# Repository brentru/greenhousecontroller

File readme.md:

# Greenhouse Control System
##  Project for ECE388

----
## Hardware

Greenboard: Control board for small-scale greenhouse control running off an ATMEGA328P.

----
## Software
Production: ATMEL Studio 7
Proto: Arduino 

----
## thanks
* David A.
* Jarred T.
* Brent R.

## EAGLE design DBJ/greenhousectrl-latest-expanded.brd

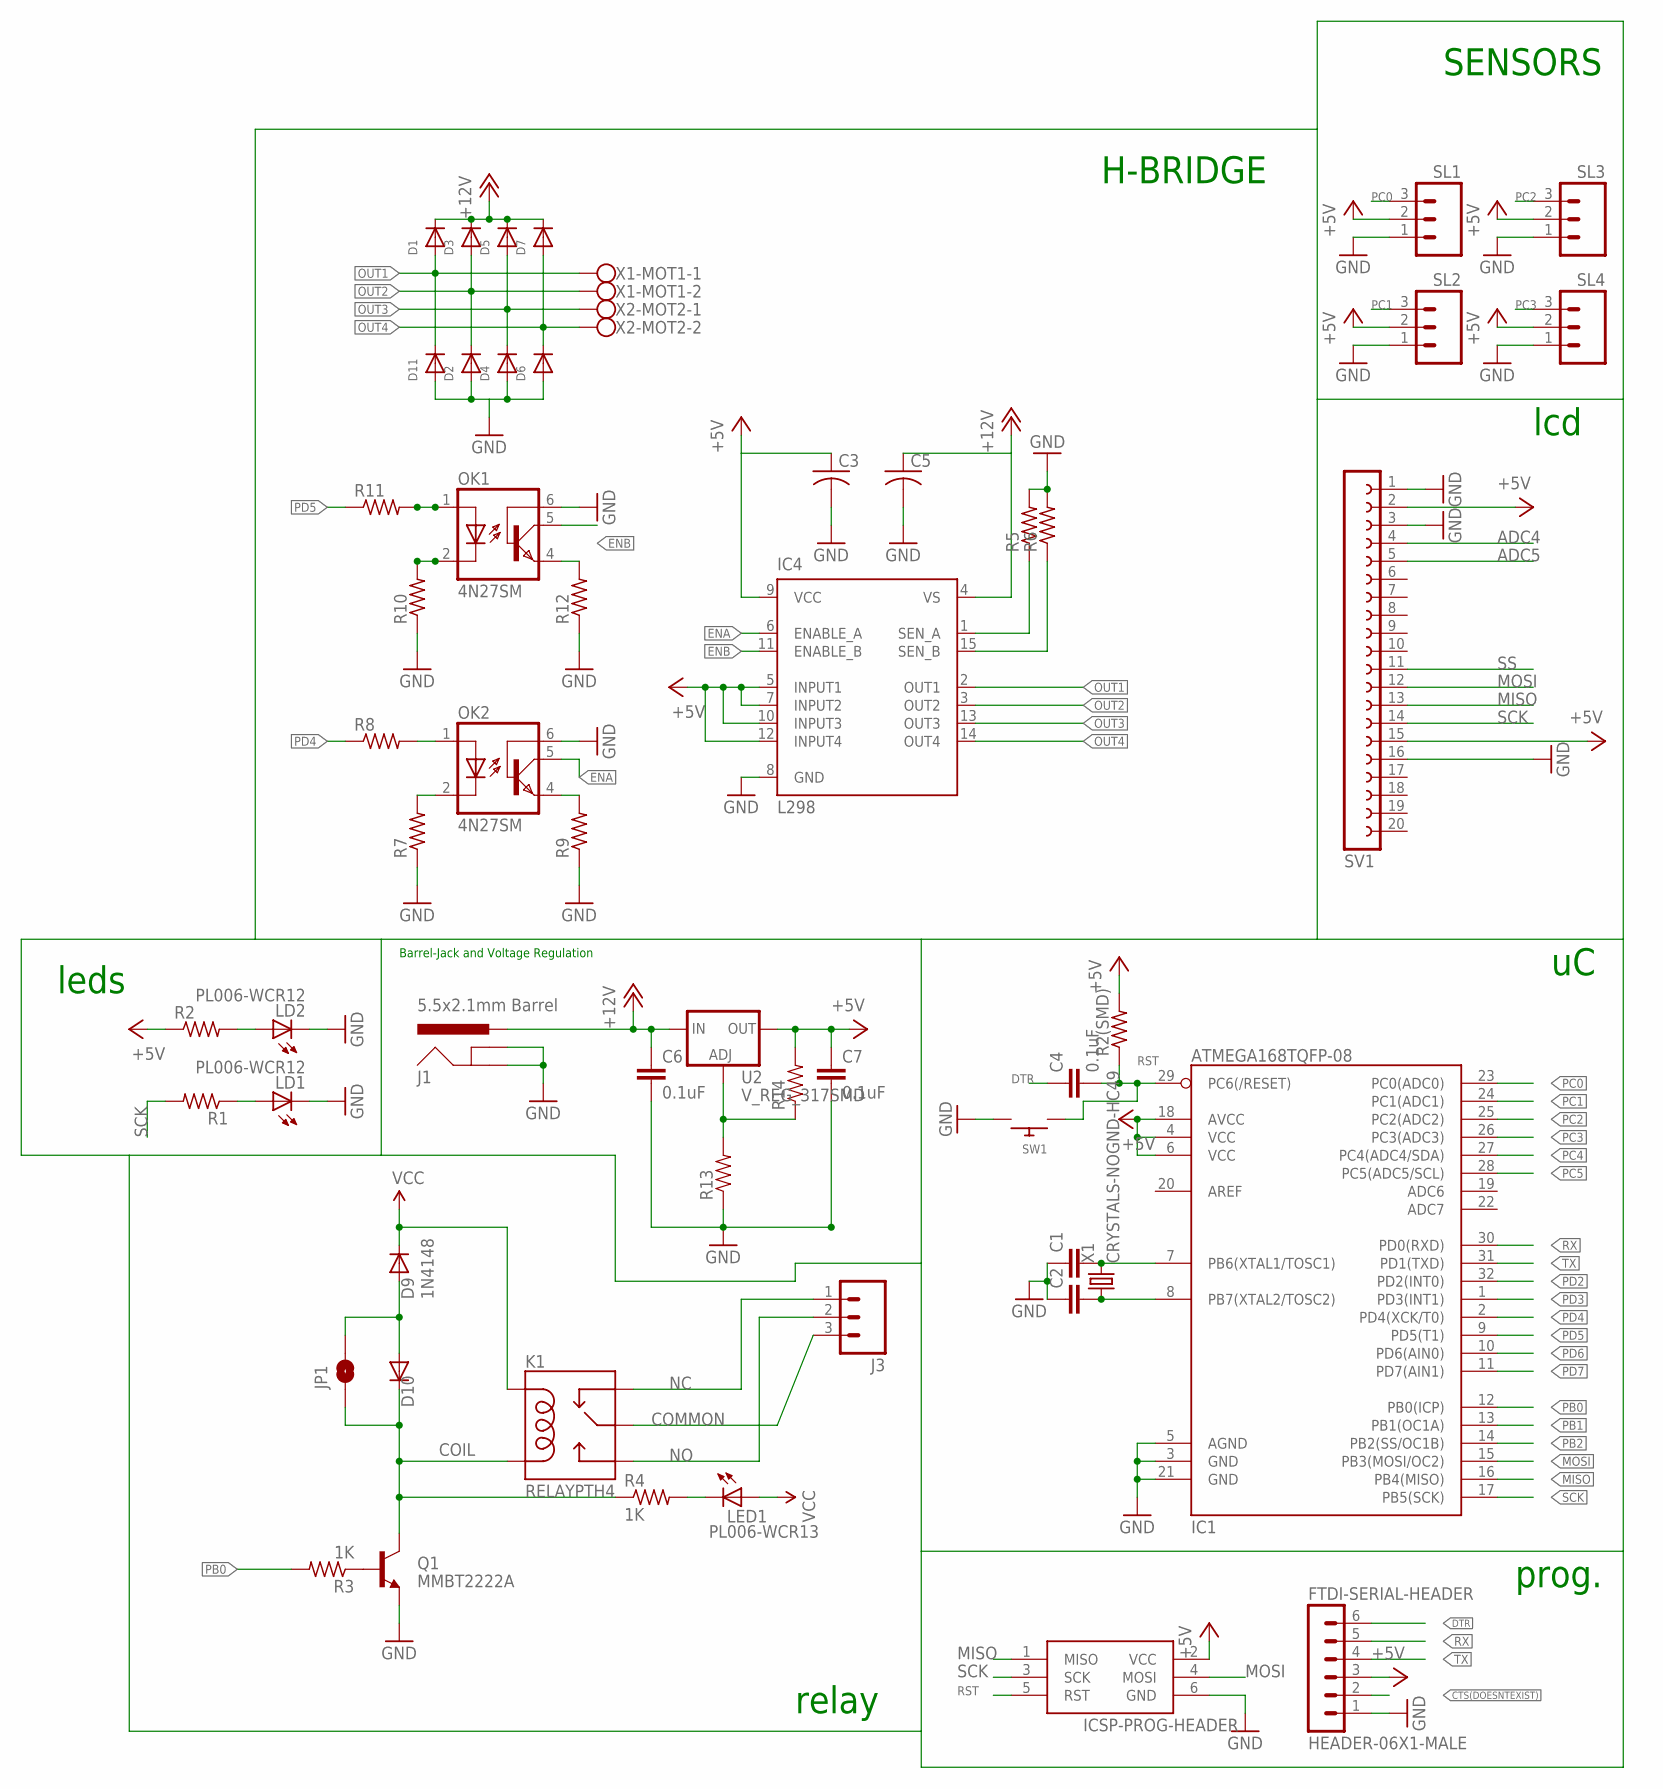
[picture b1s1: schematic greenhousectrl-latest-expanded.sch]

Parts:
C1, C2: C-EUC0805; C0805
C3, C5: C-US025-024X044; C025-024X044
C4, C6, C7: 0.1uF; 0603-CAP
D1, D2, D3, D4, D5, D6, D7, D11: DIODESOD-523; SOD-523
D9: 1N4148; SOD-323F
D10: Zener; SOD-323F
FTDI-SERIAL-HEADER: HEADER-06X1-MALE; 06X1-PTH
IC1: ATMEGA168TQFP-08; TQFP32-08
IC4: L298; MULTIWATT-15
ICSP-PROG-HEADER: AVRISP-6; AVRISP
J1: 5.5x2.1mm Barrel; POWER_JACK_SMD
J3: M03-SCREW-5MM; SCREWTERMINAL-5MM-3
JP1: JUMPER-PAD-2-NOYES_SILK; PAD-JUMPER-2-NO_YES_SILK
K1: RELAYPTH4; RELAY-JZC
LD1, LD2: PL006-WCR12; SOT23
LED1: PL006-WCR13; SOT23
OK1, OK2: 4N27SM; DIL6-SMD
Q1: MMBT2222A; SOT23-3
R1, R2, R2(SMD), R5, R6, R7, R8, R9, R10, R11, R12: R-US_M0805; M0805
R3, R4: 1K; M0805
R13, R14: RESISTOR0402; 0402-RES
SL1, SL2, SL3, SL4: M03; 03P
SV1: FE20-1; FE20
SW1: SWITCH_PUSHBUTTONC&K_KSS; BTN_CK_KSS
U2: V_REG_317SMD; SOT223
X1: CRYSTALS-NOGND-HC49; HC49
X1-MOT1, X2-MOT2: W237-102

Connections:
+5V: C3.1, C7.1, FTDI-SERIAL-HEADER.3, IC1.4 (VCC), IC1.6 (VCC), IC1.18 (AVCC), IC4.5 (INPUT1), IC4.7 (INPUT2), IC4.9 (VCC), IC4.10 (INPUT3), IC4.12 (INPUT4), ICSP-PROG-HEADER.2 (VCC), R2.1, R2(SMD).2, R14.2, SL1.2, SL2.2, SL3.2, SL4.2, SV1.2, SV1.15, U2.2 (OUT)
+12V: C5.1, C6.1, D1.K (C), D3.K (C), D5.K (C), D7.K (C), IC4.4 (VS), J1.PWR, J1.VIN0 (PWR), U2.3 (IN)
ADC4: SV1.4
ADC5: SV1.5
COIL: D10.C, JP1.1, K1.1 (COIL2), Q1.3 (C), R4.1
COMMON: J3.3, K1.4 (MAIN)
CTS(DOESNTEXIST): FTDI-SERIAL-HEADER.2
DIODENODE: D9.A, D10.A, JP1.2
DTR: C4.1, FTDI-SERIAL-HEADER.6
ENA: IC4.6 (ENABLE_A), OK2.5 (COL)
ENB: IC4.11 (ENABLE_B), OK1.5 (COL)
GND: C1.1, C2.1, C3.2, C5.2, C6.2, C7.2, D2.A, D4.A, D6.A, D11.A, FTDI-SERIAL-HEADER.1, IC1.3 (GND), IC1.5 (AGND), IC1.21 (GND), IC4.8 (GND), ICSP-PROG-HEADER.6 (GND), J1.GND (GNDBREAK), J1.GNDBREAK, J1.P$4 (GND), LD1.3 (C), LD2.3 (C), OK1.6 (BAS), OK2.6 (BAS), Q1.2 (E), R5.2, R6.2, R7.1, R9.1, R10.1, R12.1, R13.1, SL1.1, SL2.1, SL3.1, SL4.1, SV1.1, SV1.3, SV1.16, SW1.P$2
MISO: IC1.16 (PB4(MISO)), ICSP-PROG-HEADER.1 (MISO), SV1.13
MOSI: IC1.15 (PB3(MOSI/OC2)), ICSP-PROG-HEADER.4 (MOSI), SV1.12
unnamed: OK2.1 (A), R8.2
unnamed: LD2.1 (A), R2.2
unnamed: LED1.3 (C), R4.2
unnamed: OK2.2 (C), R7.2
unnamed: OK2.4 (EMI), R9.2
unnamed: Q1.1 (B), R3.1
unnamed: R13.2, R14.1, U2.1 (ADJ)
unnamed: OK1.1 (A), R11.2
unnamed: OK1.2 (C), R10.2
unnamed: LD1.1 (A), R1.1
unnamed: C1.2, IC1.7 (PB6(XTAL1/TOSC1)), X1.2
unnamed: C2.2, IC1.8 (PB7(XTAL2/TOSC2)), X1.1
unnamed: OK1.4 (EMI), R12.2
NC: J3.1, K1.2 (NC)
NO: J3.2, K1.3 (NO)
OUT1: D1.A, D11.K (C), IC4.2 (OUT1), X1-MOT1.1
OUT2: D2.K (C), D3.A, IC4.3 (OUT2), X1-MOT1.2
OUT3: D4.K (C), D5.A, IC4.13 (OUT3), X2-MOT2.1
OUT4: D6.K (C), D7.A, IC4.14 (OUT4), X2-MOT2.2
PB0: IC1.12 (PB0(ICP)), R3.2
PB1: IC1.13 (PB1(OC1A))
PB2: IC1.14 (PB2(SS/OC1B))
PC0: IC1.23 (PC0(ADC0)), SL1.3
PC1: IC1.24 (PC1(ADC1)), SL2.3
PC2: IC1.25 (PC2(ADC2)), SL3.3
PC3: IC1.26 (PC3(ADC3)), SL4.3
PC4: IC1.27 (PC4(ADC4/SDA))
PC5: IC1.28 (PC5(ADC5/SCL))
PD2: IC1.32 (PD2(INT0))
PD3: IC1.1 (PD3(INT1))
PD4: IC1.2 (PD4(XCK/T0)), R8.1
PD5: IC1.9 (PD5(T1)), R11.1
PD6: IC1.10 (PD6(AIN0))
PD7: IC1.11 (PD7(AIN1))
RST: C4.2, IC1.29 (PC6(/RESET)), ICSP-PROG-HEADER.5 (RST), R2(SMD).1, SW1.P$1
RX: FTDI-SERIAL-HEADER.5, IC1.30 (PD0(RXD))
SCK: IC1.17 (PB5(SCK)), ICSP-PROG-HEADER.3 (SCK), R1.2, SV1.14
SEN_A: IC4.1 (SEN_A), R5.1
SEN_B: IC4.15 (SEN_B), R6.1
SS: SV1.11
TX: FTDI-SERIAL-HEADER.4, IC1.31 (PD1(TXD))
VCC: D9.C, K1.5 (COIL1), LED1.1 (A)

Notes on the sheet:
Barrel-Jack and Voltage Regulation
H-BRIDGE
lcd
SENSORS
prog.
relay
leds

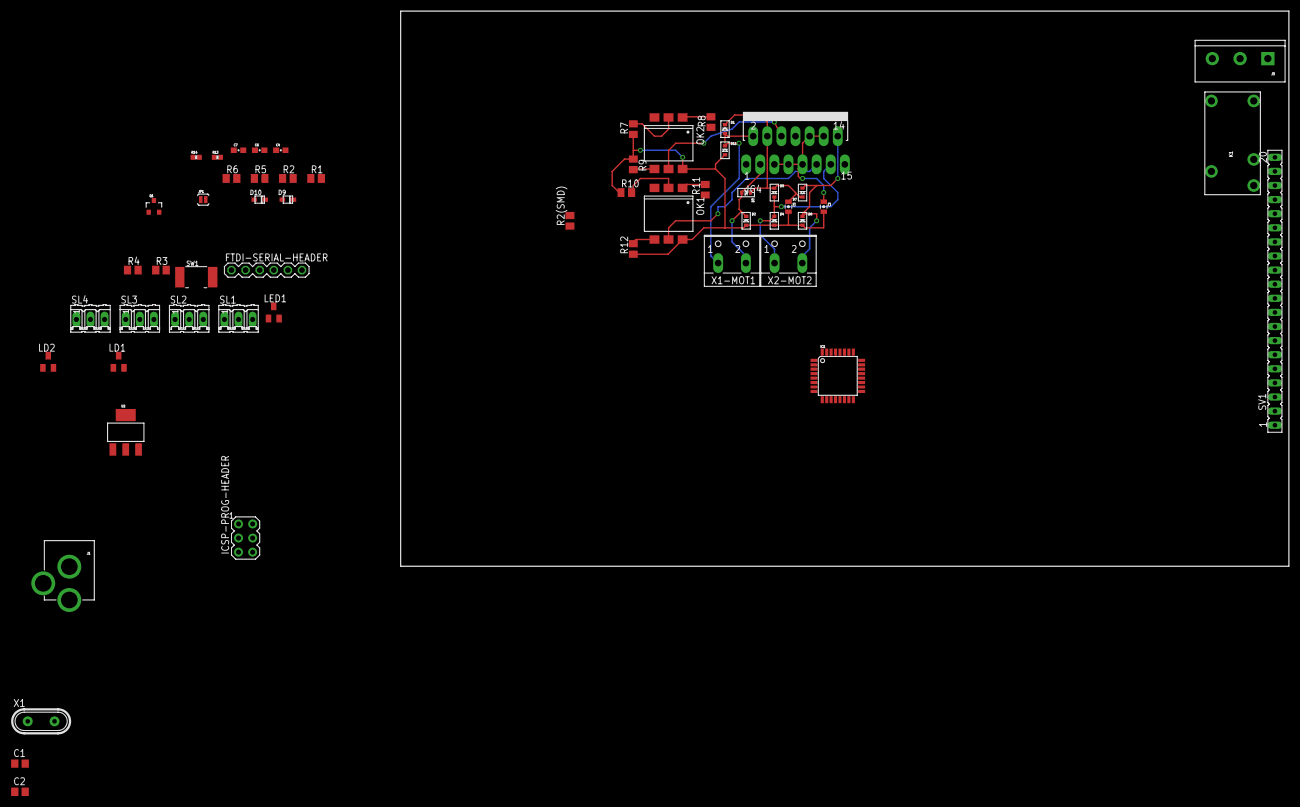
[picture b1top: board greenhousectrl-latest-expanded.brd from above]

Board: 2 copper layers, 160.0 x 100.0 mm, 56 parts (0 on the bottom side), 44 nets.

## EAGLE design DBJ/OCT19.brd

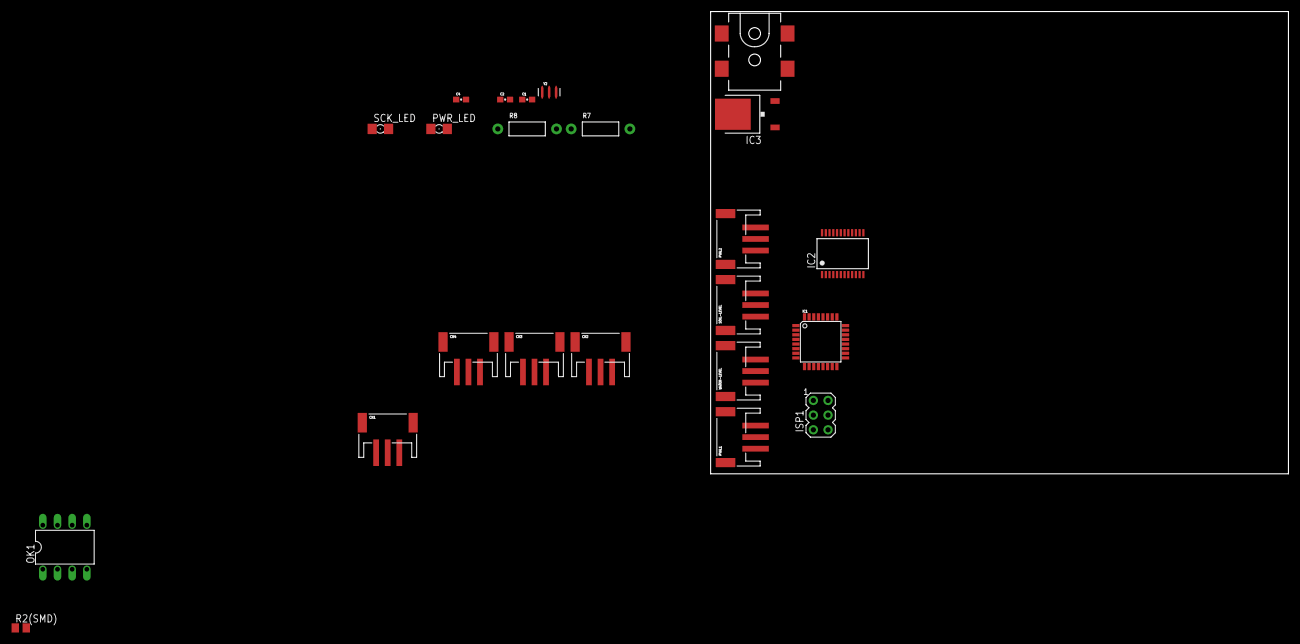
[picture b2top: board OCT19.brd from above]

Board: 2 copper layers, 100.0 x 80.0 mm, 24 parts (0 on the bottom side), 15 nets, no tracks yet.

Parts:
C1, C2, C4: 0.1uF; 0603-CAP
CN1, CN2, CN3, CN4: JSTPH3
FRAME1: FRAME-LEDGER; CREATIVE_COMMONS
IC1: ATMEGA168TQFP-08; TQFP32-08
IC2: TB6612FNG; SSOP24
IC3: 7805DT; TO252
ISP1: AVRISP-6; AVRISP
J1: 5.5x2.1mm Barrel; POWER_JACK_SMD
OK1: PC827; DIL08
PVAL1, PVAL2: JSTPH3
PWR_LED: LED_1206
R2(SMD): M0805
R7, R8: AXIAL-0.4
SCK_LED: LED_1206
SOIL-LEVEL: JSTPH3
WATER-LEVEL: JSTPH3
Y2: 16MHZ; RESONATOR-SMD

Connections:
+5V: C1.1, IC1.4, IC1.6, IC1.18, IC3.2, ISP1.2, PVAL1.2, PVAL2.2, PWR_LED.A, R2(SMD).2, SOIL-LEVEL.2, WATER-LEVEL.2
+12V: C2.1, IC3.1, J1.VIN0
GND: C1.2, C2.2, C4.1, IC1.3, IC1.5, IC1.21, IC2.18, IC3.3, ISP1.6, J1.GND, J1.P$4, PVAL1.3, PVAL2.3, R8.P$2, SCK_LED.C, SOIL-LEVEL.3, WATER-LEVEL.3, Y2.2
MISO: IC1.16, ISP1.1
MOSI: IC1.15, ISP1.4
unnamed: C4.2, IC1.29, ISP1.5, R2(SMD).1
unnamed: R7.P$2, SCK_LED.A
unnamed: PWR_LED.C, R8.P$1
PC0: IC1.23, PVAL1.1
PC1: IC1.24, PVAL2.1
PC2: IC1.25, SOIL-LEVEL.1
PC3: IC1.26, WATER-LEVEL.1
SCK: IC1.17, ISP1.3, R7.P$1
XTAL1: IC1.7, Y2.3
XTAL2: IC1.8, Y2.1

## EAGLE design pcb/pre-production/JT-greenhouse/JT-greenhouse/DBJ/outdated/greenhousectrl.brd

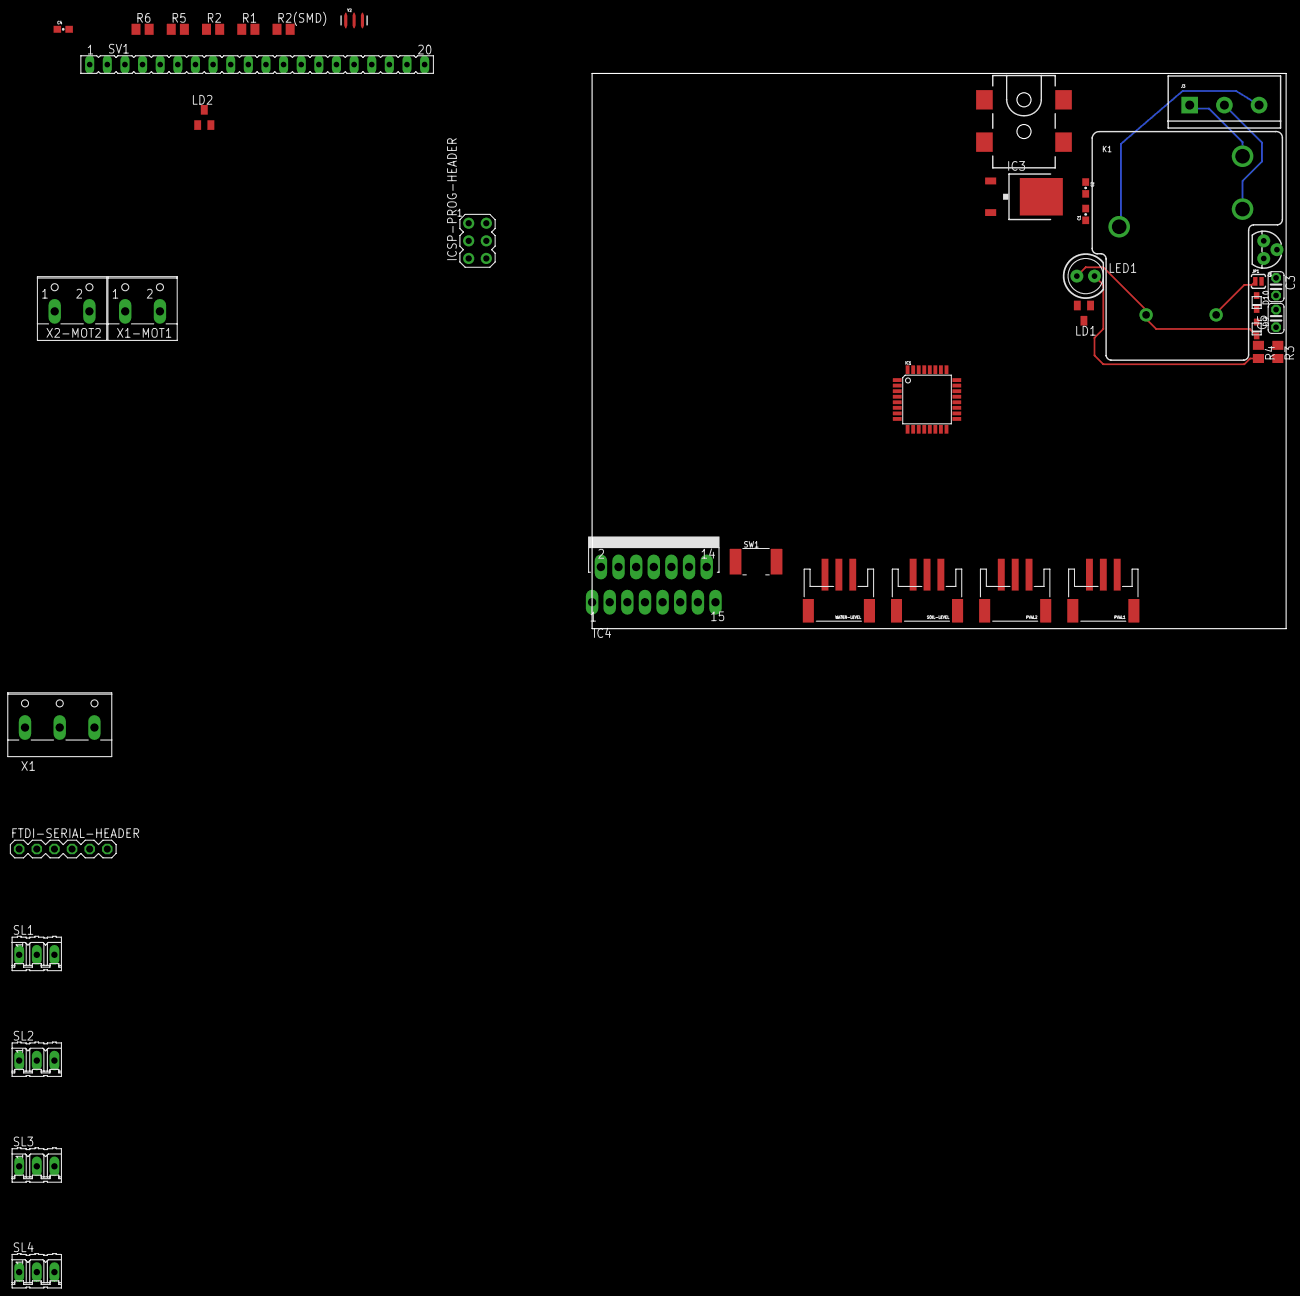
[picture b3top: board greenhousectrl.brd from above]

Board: 2 copper layers, 100.0 x 80.0 mm, 41 parts (0 on the bottom side), 35 nets.

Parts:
C1, C2, C4: 0.1uF; 0603-CAP
C3, C5: C025-024X044
D9: 1N4148; SOD-323F
D10: Zener; SOD-323F
FTDI-SERIAL-HEADER: HEADER-06X1-MALE; 06X1-PTH
IC1: ATMEGA168TQFP-08; TQFP32-08
IC3: 7805DT; TO252
IC4: L298; MULTIWATT-15
ICSP-PROG-HEADER: AVRISP-6; AVRISP
J1: 5.5x2.1mm Barrel; POWER_JACK_SMD
J3: SCREWTERMINAL-5MM-3
JP1: JUMPER-PAD-2-NOYES_SILK; PAD-JUMPER-2-NO_YES_SILK
K1: JQX-15F; RELAY-T90
LD1, LD2: PL006-WCR12; SOT23
LED1: LED5MM-KIT
PVAL1, PVAL2: JSTPH3
Q1: 2N3904; TO-92-EZ
R1, R2, R2(SMD), R5, R6: M0805
R3, R4: 1K; M0805
SL1, SL2, SL3, SL4: 03P
SOIL-LEVEL: JSTPH3
SV1: FE20
SW1: BTN_CK_KSS
WATER-LEVEL: JSTPH3
X1: W237-103
X1-MOT1, X2-MOT2: W237-102
Y2: 16MHZ; RESONATOR-SMD

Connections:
+5V: C1.1, C3.1, FTDI-SERIAL-HEADER.3, IC1.4, IC1.6, IC1.18, IC3.2, IC4.5, IC4.7, IC4.9, IC4.10, IC4.12, ICSP-PROG-HEADER.2, PVAL1.2, PVAL2.2, R2.1, R2(SMD).2, SOIL-LEVEL.2, SV1.2, SV1.15, WATER-LEVEL.2
+12V: C2.1, C5.1, IC3.1, IC4.4, J1.VIN0
COIL: D10.C, JP1.1, K1.COIL2, Q1.3, R4.1
COMMON: J3.3, K1.MAIN
DIODENODE: D9.A, D10.A, JP1.2
DTR: C4.1, FTDI-SERIAL-HEADER.6
GND: C1.2, C2.2, C3.2, C5.2, FTDI-SERIAL-HEADER.1, IC1.3, IC1.5, IC1.21, IC3.3, IC4.8, ICSP-PROG-HEADER.6, J1.GND, J1.P$4, LD1.3, LD2.3, PVAL1.3, PVAL2.3, Q1.1, R5.2, R6.2, SOIL-LEVEL.3, SV1.1, SV1.3, SV1.16, SW1.P$2, WATER-LEVEL.3, Y2.2
MISO: IC1.16, ICSP-PROG-HEADER.1, SV1.13
MOSI: IC1.15, ICSP-PROG-HEADER.4, SV1.12
unnamed: LD2.1, R2.2
unnamed: LED1.K, R4.2
unnamed: Q1.2, R3.1
unnamed: IC4.2, X2-MOT2.2
unnamed: IC4.13, X1-MOT1.2
unnamed: IC4.14, X1-MOT1.1
unnamed: LD1.1, R1.1
unnamed: IC1.7, Y2.1
unnamed: IC4.1, R5.1
unnamed: IC4.15, R6.1
unnamed: IC4.3, X2-MOT2.1
unnamed: IC1.8, Y2.3
NC: J3.1, K1.NC
NO: J3.2, K1.NO
PB0: IC1.12, R3.2
PC0: IC1.23, PVAL1.1
PC1: IC1.24, PVAL2.1
PC2: IC1.25, SOIL-LEVEL.1
PC3: IC1.26, WATER-LEVEL.1
PD4: IC1.2, IC4.6
PD5: IC1.9, IC4.11
RST: C4.2, IC1.29, ICSP-PROG-HEADER.5, R2(SMD).1, SW1.P$1
RX: FTDI-SERIAL-HEADER.5, IC1.30
SCK: IC1.17, ICSP-PROG-HEADER.3, R1.2, SV1.14
TX: FTDI-SERIAL-HEADER.4, IC1.31
VCC: D9.C, K1.COIL1, LED1.A

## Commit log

2016-10-20 readme commit
    added readme
2016-10-20 Add files via upload
    Still working on the schematic for the chip, this is what I have so far
2016-10-21 thursnightchanges
    added jsts area, redid labels on right side of chip
2016-10-23 Hbridge
    entire hbridge circuit, changed any remaining thru-hole to smd, used a
    different hbridge, organized the schematic,
2016-10-23 Add files via upload
    Redid the crystal wiring, and edited the RST of the ICSP
2016-10-24 sunday changes
    added a push button to pc6/reset for human-interaction with the reset
    line
2016-10-24 removed octocouplers
    Removed octocouplers due to redundancy. IC can handle 12V and 5V, won’t
    fry anything.
2016-10-24 Add files via upload
    First attempt: Created nets, named them after the appropriate microcontroller connections, and "wired" them to a 20-pin female header for IDE.
2016-10-25 Add files via upload
    Updated with the assistance from Dave, as well as with the relay setup.
2016-10-25 rev 0.0.1 of schematic
    first rev of full schematic capture
2016-10-27 in-lab sync
2016-10-27 Optocouplers
    hbridge now has a better octocoupler circuit attached
2016-10-27 board updated
    traces added for flyback diodes
2016-10-29 Updated Schematic Notes
    smaller relay, smd parts added for leds instead of thru-hole, smaller
    diodes for h-bridge
2016-10-29 Updated Schematic
    clearly shows subsystems for pcb layout
2016-11-01 Add files via upload
    Modifications to Dave's revisions.
2016-11-02 In Lab changes
2016-11-02 Expansion of Board
    Worked on reorganizing the h-bridge and components
2016-11-02 Reorg of files and added expanded board design
2016-11-04 Updated power jack / caps, routed h-bridge and components
2016-11-04 replaced parts to conform with preferred part list
2016-11-04 Add files via upload
    Modifications to listed components
2016-11-06 Saturday Update
    routed/organized: voltage regulator, barrel jack, relay
2016-11-06 Compressed the components near and around h-bridge
2016-11-06 Saturday Update
    Board sz reduction. uC, sensors, and GND needs to be routed. Ground
    plane (top/bot) added.
2016-11-06 Sunday Revisions
2016-11-07 erc and new vreg
    ran erc on schematic, re-organized repository, used 7824DTvreg instead
    of the vreg previously used due to erc giving errors
2016-11-07 Ran Dirty8TS, fixed wiring and angle errors
2016-11-07 no drc errors
2016-11-07 Swapped out sensor pins
2016-11-08 Replaced 1x20 LCD with 2 1x8, gerb and DRC checked
2016-11-08 Fixed Orientation of Jack, New Gerb Files and Updated Folder for Viall
2016-11-08 production files first ul
2016-11-08 Redid Gerbv and Gerbers, Created Folder for Items Viall Requested
2016-11-19 Moved Most Recent Board Design and Gerbers with thebom into git
2016-11-19 Moved Components on Right side down for heat sink, added drill holes for heat sink
2016-11-19 Changes, 6 errors left
2016-11-19 fixedERRS
2016-11-19 Updated Gerbv and Gerber Files, Copied Folder to Google Drive
2016-11-21 Added correct H bridge, corrected some of ben's suggestions
2016-11-21 Fixed Traces
2016-11-21 Replaced H-bridge, remapped pins where needed. Needs routing still
2016-11-21 Add files via upload
    H-Bridge revisions. Still a minor questionable piece (refer to errors)
2016-11-22 Add files via upload
    Latest revision: No errors, no airwires
2016-11-22 Finalized with Gerbers and Gerbv along with Updated BOM
    Sent to Ben, for production of board
2016-11-22 Added Frame Ledger
2016-11-29 file directories moved
2016-11-29 first firmware push
2016-11-30 Referenced Code
2016-12-02 Updated LCD Code
2016-12-05 Update LICENSE
2016-12-13 project submit sub-section
2016-12-13 new case added and bug fixes
2017-03-15 cleaned up repo

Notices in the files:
parts and their libraries:
SparkFun-Capacitors: Licensing: Creative Commons ShareAlike 4.0 International - https://creativecommons.org/licenses/by-sa/4.0
SparkFun-Aesthetics: Released under the Creative Commons Attribution Share-Alike 4.0 License
SparkFun-Aesthetics: https://creativecommons.org/licenses/by-sa/4.0
